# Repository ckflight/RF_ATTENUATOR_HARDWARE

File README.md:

# RF_ATTENUATOR_HARDWARE

1 to 6000MHz 7-Bit Digital Step Attenuator Board with Parallel or Serial Interface.

Max 30-32dBm Peak Input Power and 31.75 dB attenuation range.

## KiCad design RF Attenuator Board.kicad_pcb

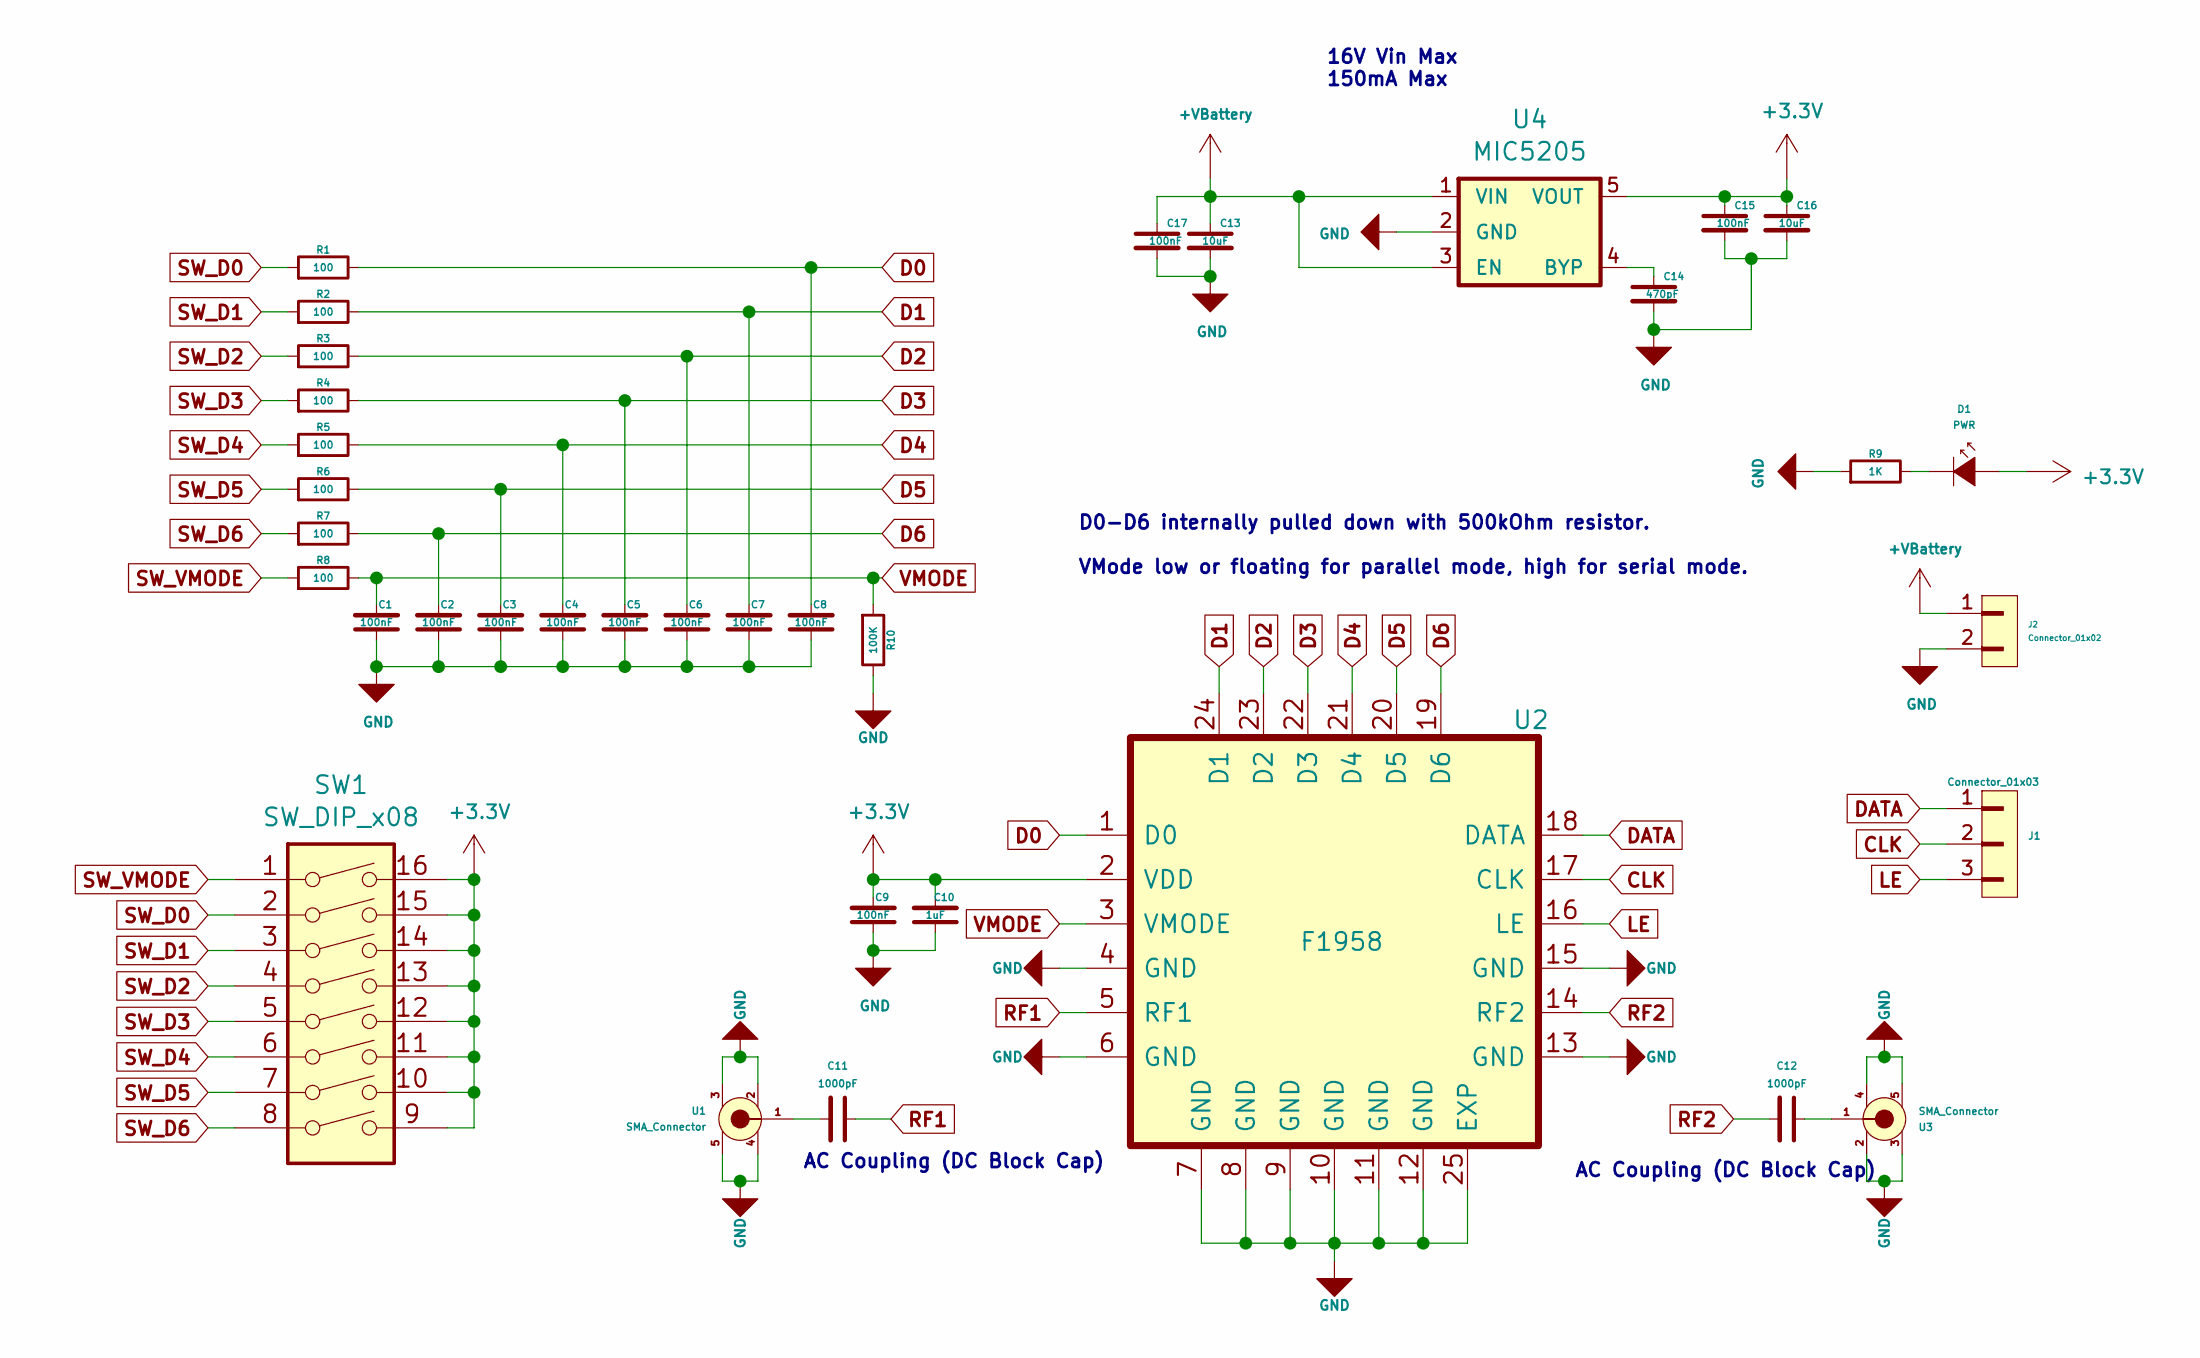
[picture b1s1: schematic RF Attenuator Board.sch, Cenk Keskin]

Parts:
C1, C2, C3, C4, C5, C6, C7, C8, C9, C15, C17: 100nF; SMD_0402
C10: 1uF; SMD_0402
C11, C12: 1000pF; SMD_0402
C13, C16: 10uF; SMD_0402
C14: 470pF; SMD_0402
D1: PWR; Diode_0603
J1: Connector_01x03; PinHeader_1x3_P2.54mm
J2: Connector_01x02; PinHeader_1x2_P2.54mm
R1, R2, R3, R4, R5, R6, R7, R8: 100; SMD_0402
R9: 1K; SMD_0402
R10: 100K; SMD_0402
SW1: SW_DIP_x08; DIP_SWITCH_x8_A6H_8101
U1, U3: SMA_Connector
U2: F1958; QFN24_4x4mm_P0.5mm_1EXP_2.7x2.7mm
U4: MIC5205; SOT23_5

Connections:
+3V3: C9.2, C10.2, C15.1, C16.1, D1.2 (A), SW1.9, SW1.10, SW1.11, SW1.12, SW1.13, SW1.14, SW1.15, SW1.16, U2.2 (VDD), U4.5 (VOUT); also elsewhere on the board
+VBattery: C13.1, C17.1, J2.1, U4.1 (VIN), U4.3 (EN)
CLK: J1.2, U2.17 (CLK)
D0: C8.2, R1.2, U2.1 (D0)
D1: C7.2, R2.2, U2.24 (D1)
D2: C6.2, R3.2, U2.23 (D2)
D3: C5.2, R4.2, U2.22 (D3)
D4: C4.2, R5.2, U2.21 (D4)
D5: C3.2, R6.2, U2.20 (D5)
D6: C2.2, R7.2, U2.19 (D6)
DATA: J1.1, U2.18 (DATA)
GND: C1.1, C2.1, C3.1, C4.1, C5.1, C6.1, C7.1, C8.1, C9.1, C10.1, C13.2, C14.2, C15.2, C16.2, C17.2, J2.2, R9.1, R10.2, U1.2, U1.3, U1.4, U1.5, U2.4 (GND), U2.6 (GND), U2.7 (GND), U2.8 (GND), U2.9 (GND), U2.10 (GND), U2.11 (GND), U2.12 (GND), U2.13 (GND), U2.15 (GND), U2.25 (EXP), U3.2, U3.3, U3.4, U3.5, U4.2 (GND)
LE: J1.3, U2.16 (LE)
unnamed: C11.2, U1.1
unnamed: C12.1, U3.1
unnamed: C14.1, U4.4 (BYP)
unnamed 16: D1.1 (K), R9.2; also elsewhere on the board
RF1: C11.1, U2.5 (RF1)
RF2: C12.2, U2.14 (RF2)
SW_D0: R1.1, SW1.2
SW_D1: R2.1, SW1.3
SW_D2: R3.1, SW1.4
SW_D3: R4.1, SW1.5
SW_D4: R5.1, SW1.6
SW_D5: R6.1, SW1.7
SW_D6: R7.1, SW1.8
SW_VMODE: R8.1, SW1.1
VMODE: C1.2, R8.2, R10.1, U2.3 (VMODE)

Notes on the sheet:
D0-D6 internally pulled down with 500kOhm resistor.
VMode low or floating for parallel mode, high for serial mode.
AC Coupling (DC Block Cap)
16V Vin Max 150mA Max

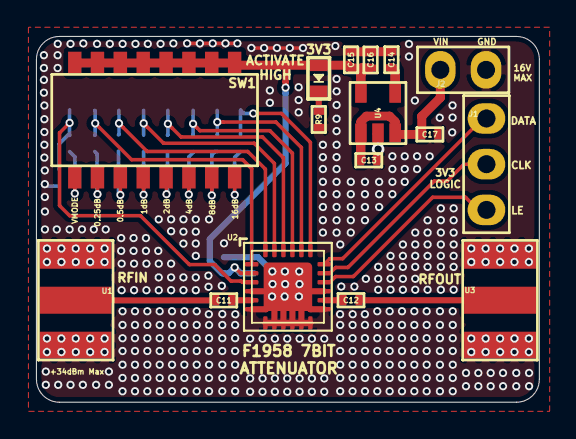
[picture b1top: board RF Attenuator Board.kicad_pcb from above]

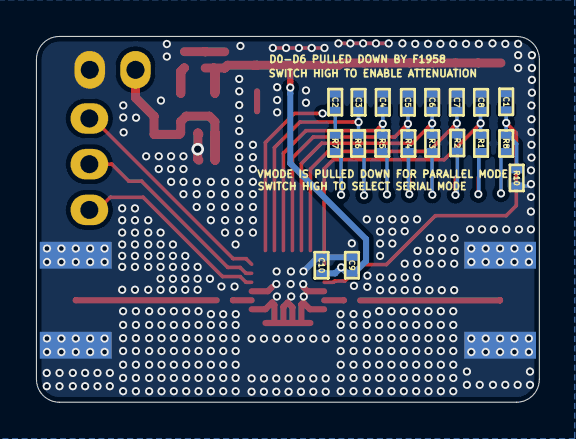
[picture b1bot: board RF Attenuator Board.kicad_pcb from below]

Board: 4 copper layers, 27.9 x 20.3 mm, 35 parts (19 on the bottom side), 28 nets.

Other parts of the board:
3V3: PWR; Diode_0603

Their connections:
+3V3: 3V3.2; also elsewhere on the board
unnamed 16: 3V3.1; also elsewhere on the board
